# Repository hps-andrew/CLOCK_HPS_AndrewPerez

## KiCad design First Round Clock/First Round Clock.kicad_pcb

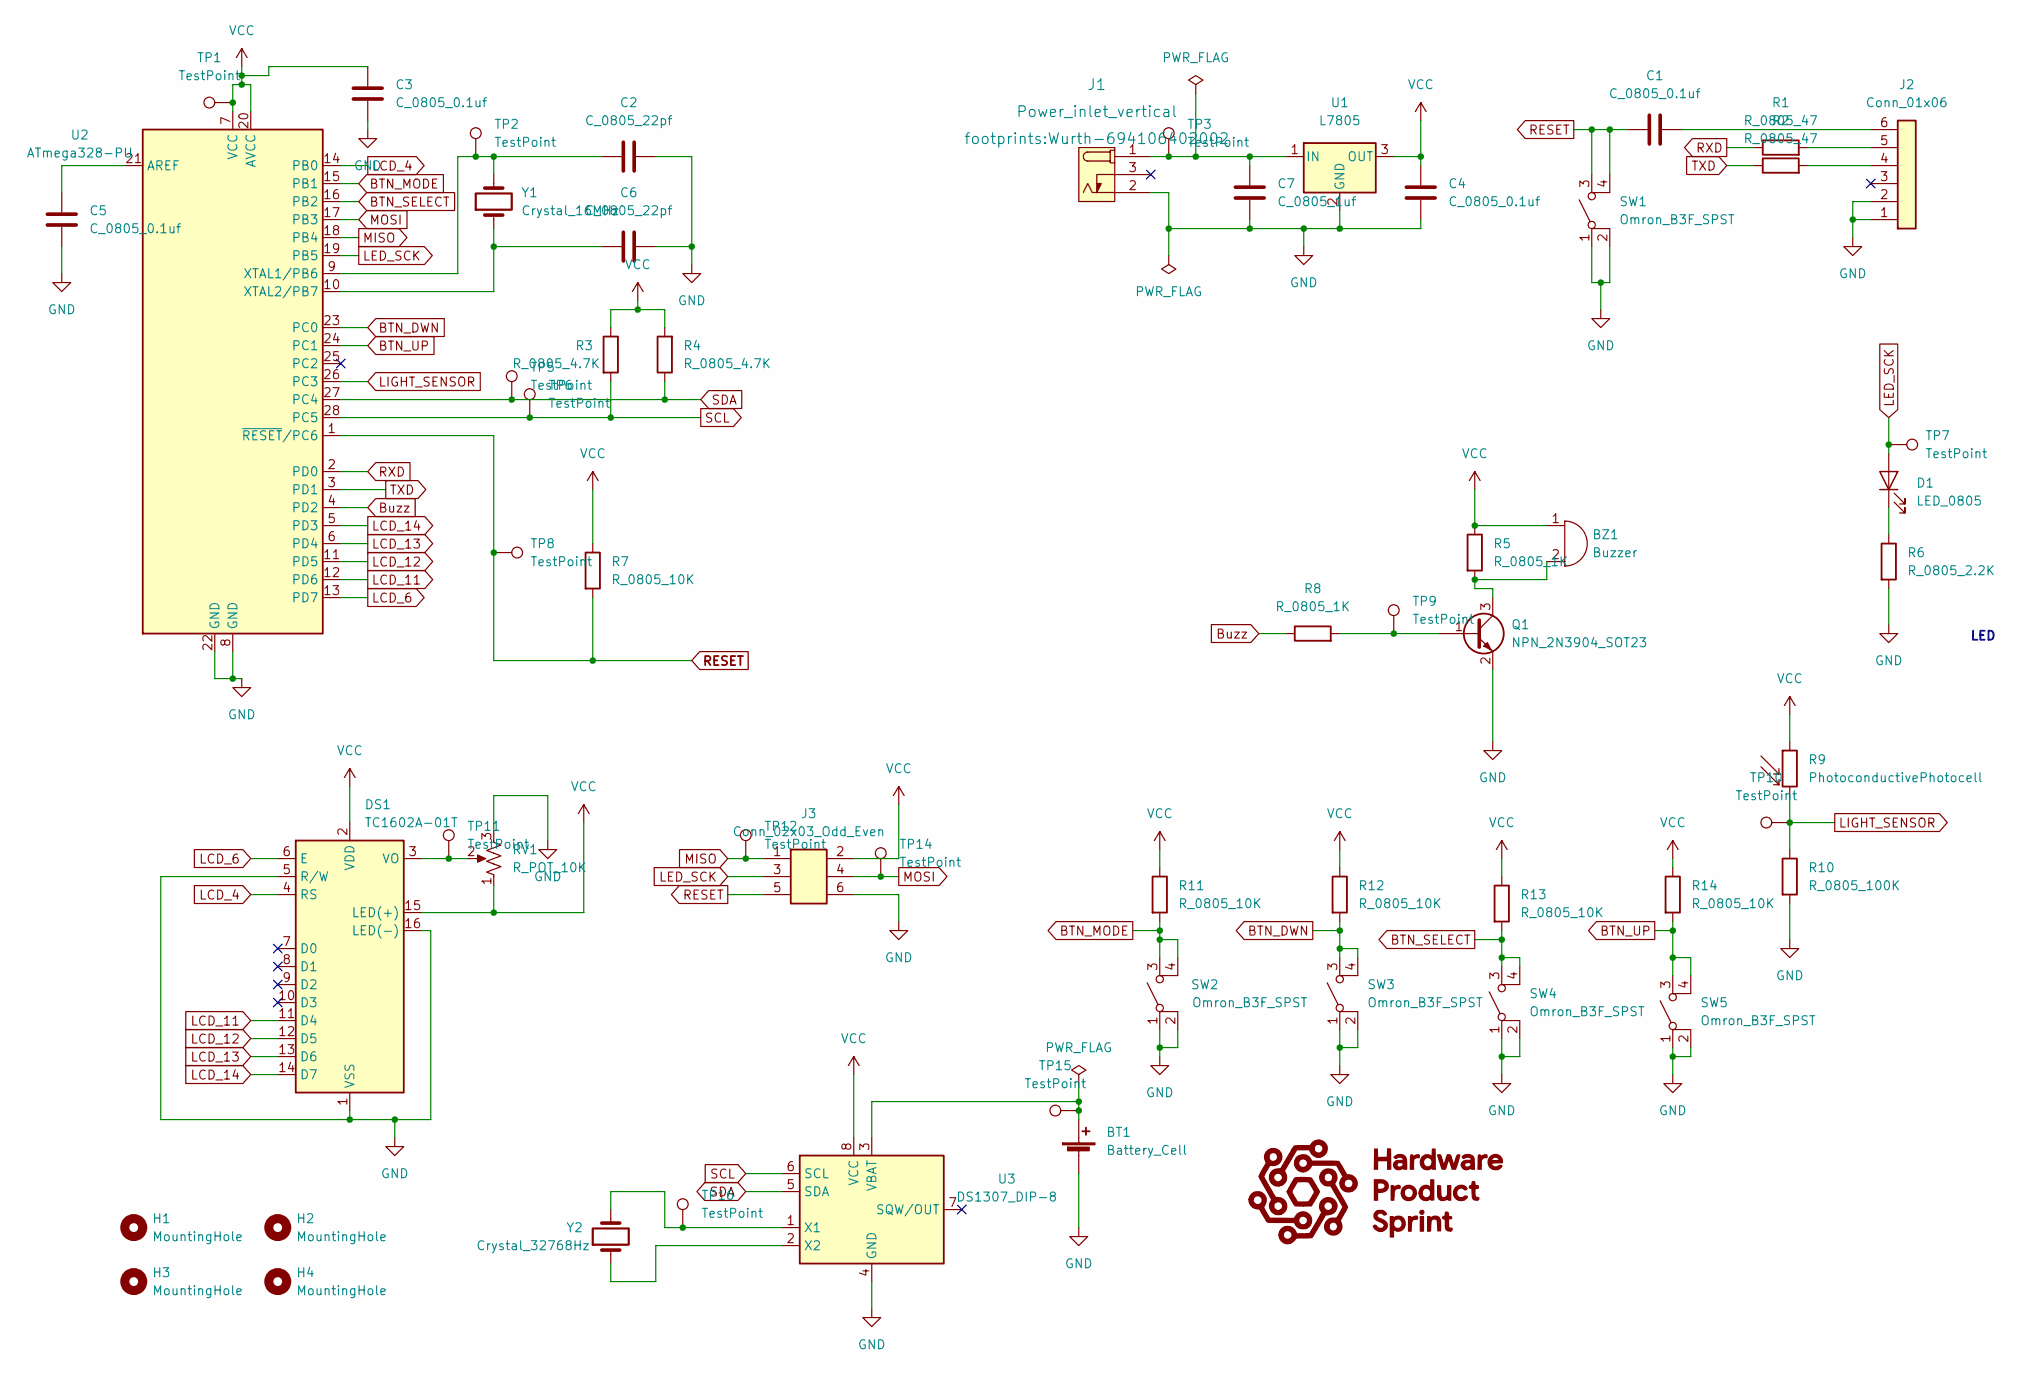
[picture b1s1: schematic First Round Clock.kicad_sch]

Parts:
BT1: Battery_Cell; BatteryHolder_Keystone_106_1x20mm; MPN BS-7; Digikey PN BS-7-ND
BZ1: Buzzer; Buzzer_TDK_PS1240P02BT_D12.2mm_H6.5mm; MPN PS1420P02CT; Digikey PN 445-2526-1-ND
C1, C3, C4, C5: C_0805_0.1uf; C_0805_2012Metric; Voltage N/A; Tolerance N/A; MPN 08055C104KAT2A; Digikey PN 478-1395-1-ND
C2, C6: C_0805_22pf; C_0805_2012Metric; Voltage N/A; Tolerance N/A; MPN CC0805JRNPO9BN220; Digikey PN 311-1103-1-ND
C7: C_0805_1uf; C_0805_2012Metric; Voltage N/A; Tolerance N/A; MPN CC0805KKX7R8BB105; Digikey PN 311-1456-1-ND
D1: LED_0805; LED_0805_2012Metric; MPN 150080RS75000; Digikey PN 732-4984-1-ND
DS1: TC1602A-01T; MPN 1447; Digikey PN 1528-2212-ND
H1, H2, H3, H4: MountingHole; MountingHole_3.2mm_M3
J1: Power_inlet_vertical; Wurth-694106402002; MPN 694106402002; Digikey PN 732-5931-ND
J2: Conn_01x06; PinHeader_1x06_P2.54mm_Vertical; MPN 61300611121; Digikey PN 732-5319-ND
J3: Conn_02x03_Odd_Even; PinHeader_2x03_P2.54mm_Vertical; MPN PRPC003DAAN-RC; Digikey PN S2011EC-03-ND
Q1: NPN_2N3904_SOT23; SOT-23; MPN CMPT3904E TR PBFREE; Digikey PN 1514-CMPT3904ETRPBFREECT-ND
R1, R2: R_0805_47; R_0805_2012Metric; Tolerance N/A; Mouser PN N/A; Digikey PN RC0805FR-0747RL
R3, R4: R_0805_4.7K; R_0805_2012Metric; Tolerance N/A; MPN RC0805FR-074K7L; Digikey PN 311-4.70KCRCT-ND
R5, R8: R_0805_1K; R_0805_2012Metric; Tolerance N/A; Mouser PN N/A; Digikey PN RC0805FR-0710KL
R6: R_0805_2.2K; R_0805_2012Metric; Tolerance N/A; MPN N/A; Digikey PN 311-2.20KCRCT-ND
R7, R11, R12, R13, R14: R_0805_10K; R_0805_2012Metric; Tolerance N/A; MPN RC0805FR-0710KL; Digikey PN 311-10.0KCRCT-ND
R9: PhotoconductivePhotocell; R_LDR_4.9x4.2mm_P2.54mm_Vertical; Voltage N/A; Tolerance N/A; MPN PDV-P8103; Digikey PN PDV-P8103-ND
R10: R_0805_100K; R_0805_2012Metric; Tolerance N/A; MPN RC0805FR-07100KL; Digikey PN 311-100KCRCT-ND
RV1: R_POT_10K; Potentiometer_Bourns_3386P_Vertical; MPN 3386P-1-103TLF; Digikey PN 3386P-103TLF-ND
SW1, SW2, SW3, SW4, SW5: Omron_B3F_SPST; SW_SPST_Omron_B3FS-100xP; MPN B3FS-1000P; Digikey PN SW423CT-ND
TP1, TP2, TP3, TP5, TP6, TP7, TP8, TP9, TP10, TP11, TP12, TP14, TP15, TP16: TestPoint; TestPoint_THTPad_D2.0mm_Drill1.0mm
U1: L7805; TO-252-2; MPN L7805CDT-TR; Digikey PN 497-7255-1-ND
U2: ATmega328-PU; DIP-28_W7.62mm; MPN ED281DT; Digikey PN ED3050-5-ND
U3: DS1307_DIP-8; DIP-8_W7.62mm; MPN A 08-LC-TT; Digikey PN AE9986-ND
Y1: Crystal_16MHz; Crystal_SMD_HC49-SD; MPN ECS-160-20-5PXDN-TR; Digikey PN XC1299CT-ND
Y2: Crystal_32768Hz; Crystal_SMD_2Pin_3.2x1.5mm; MPN Q 0,032768-JTX310-12,5-20-T1-HMR-50K-LF; Digikey PN 1908-1314-1-ND

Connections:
BTN_DWN: R12.2, SW3.3 (B), SW3.4 (B), U2.23 (PC0)
BTN_MODE: R11.2, SW2.3 (B), SW2.4 (B), U2.15 (PB1)
BTN_SELECT: R13.2, SW4.3 (B), SW4.4 (B), U2.16 (PB2)
BTN_UP: R14.2, SW5.3 (B), SW5.4 (B), U2.24 (PC1)
Buzz: R8.1, U2.4 (PD2)
GND: BT1.2 (-), C2.1, C3.2, C4.2, C5.2, C6.2, C7.2, DS1.1 (VSS), DS1.5 (R/W), DS1.16 (LED(-)), J1.2 (OUT), J2.1, J2.2, J3.6, Q1.2 (E), R6.2, R10.2, RV1.3, SW1.1 (A), SW1.2 (A), SW2.1 (A), SW2.2 (A), SW3.1 (A), SW3.2 (A), SW4.1 (A), SW4.2 (A), SW5.1 (A), SW5.2 (A), U1.2 (GND), U2.8 (GND), U2.22 (GND), U3.4 (GND)
LCD_4: DS1.4 (RS), U2.14 (PB0)
LCD_6: DS1.6 (E), U2.13 (PD7)
LCD_11: DS1.11 (D4), U2.12 (PD6)
LCD_12: DS1.12 (D5), U2.11 (PD5)
LCD_13: DS1.13 (D6), U2.6 (PD4)
LCD_14: DS1.14 (D7), U2.5 (PD3)
LED_SCK: D1.2 (A), J3.3, TP7.1, U2.19 (PB5)
LIGHT_SENSOR: R9.2, R10.1, TP10.1, U2.26 (PC3)
MISO: J3.1, TP12.1, U2.18 (PB4)
MOSI: J3.4, TP14.1, U2.17 (PB3)
unnamed: BT1.1 (+), TP15.1, U3.3 (VBAT)
unnamed: BZ1.2 (+), Q1.3 (C), R5.2
unnamed: C1.2, J2.6
unnamed: C2.2, TP2.1, U2.9 (XTAL1/PB6), Y1.2
unnamed: C5.1, U2.21 (AREF)
unnamed: C6.1, U2.10 (XTAL2/PB7), Y1.1
unnamed: D1.1 (K), R6.1
unnamed: DS1.3 (VO), RV1.2, TP11.1
unnamed: C7.1, J1.1 (POLE), TP3.1, U1.1 (IN)
unnamed: J2.4, R2.2
unnamed: J2.5, R1.2
unnamed: Q1.1 (B), R8.2, TP9.1
unnamed: TP16.1, U3.1 (X1), Y2.2
unnamed: U3.2 (X2), Y2.1
RESET: C1.1, J3.5, R7.2, SW1.3 (B), SW1.4 (B), TP8.1, U2.1 (~RESET/PC6)
RXD: R1.1, U2.2 (PD0)
SCL: R3.2, TP6.1, U2.28 (PC5), U3.6 (SCL)
SDA: R4.1, TP5.1, U2.27 (PC4), U3.5 (SDA)
TXD: R2.1, U2.3 (PD1)
VCC: BZ1.1 (-), C3.1, C4.1, DS1.2 (VDD), DS1.15 (LED(+)), J3.2, R3.1, R4.2, R5.1, R7.1, R9.1, R11.1, R12.1, R13.1, R14.1, RV1.1, TP1.1, U1.3 (OUT), U2.7 (VCC), U2.20 (AVCC), U3.8 (VCC)

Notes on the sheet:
LED

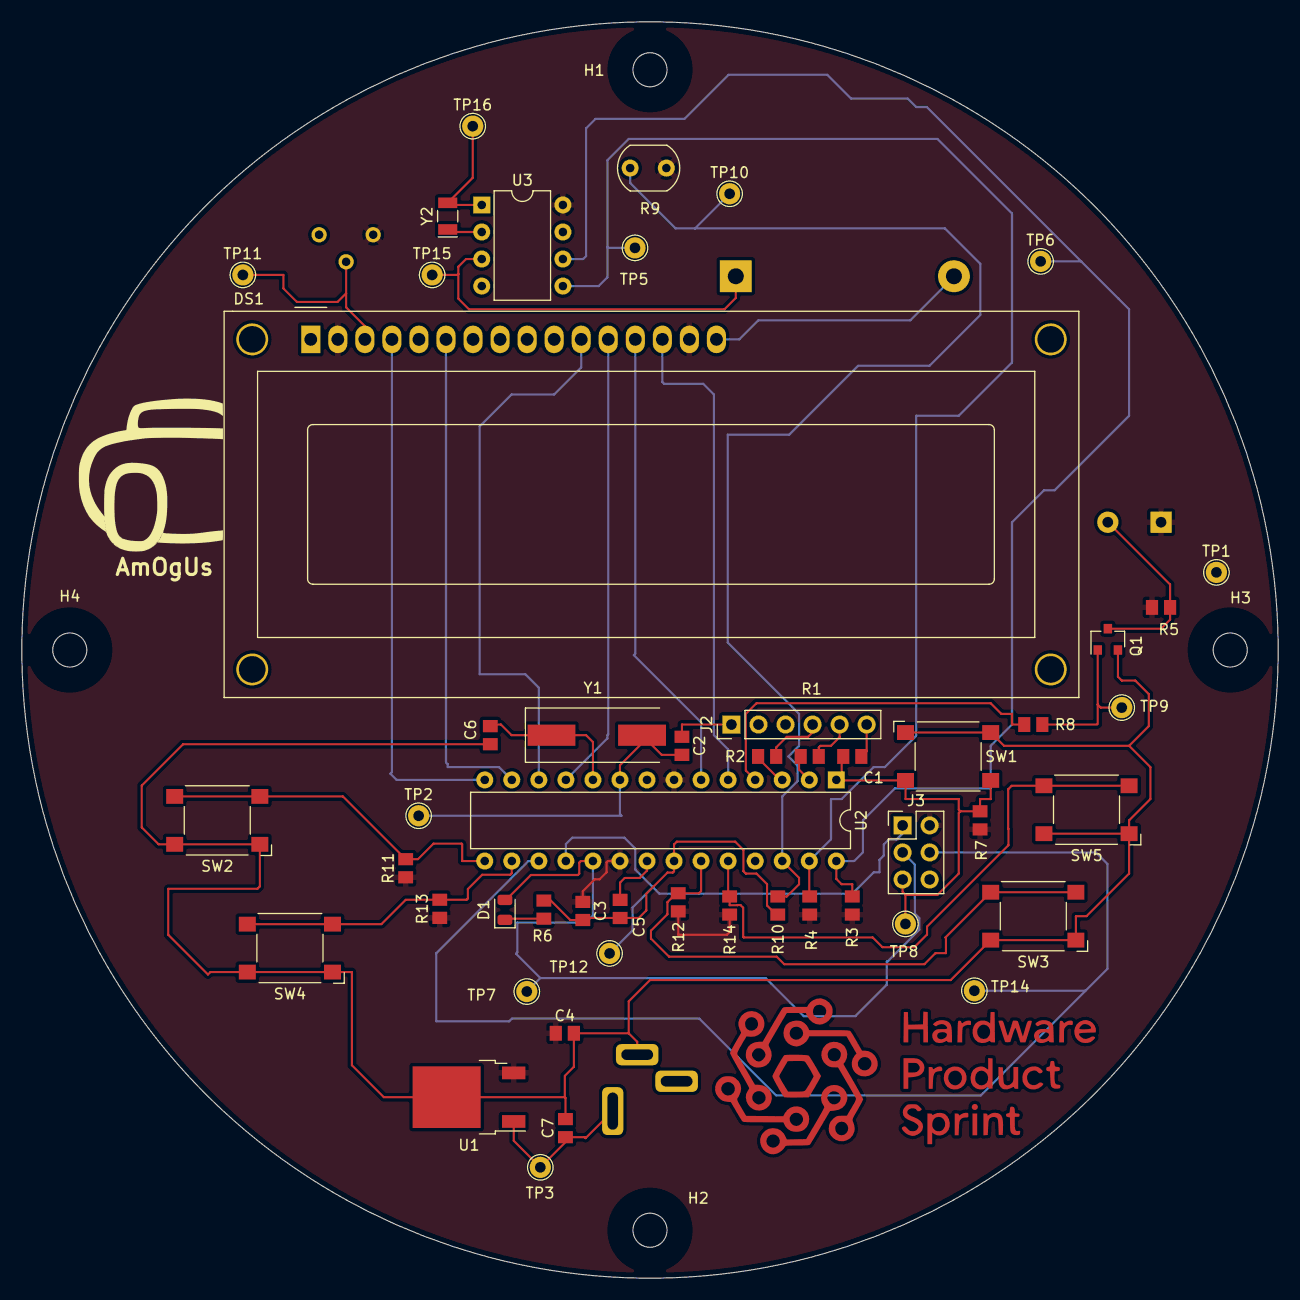
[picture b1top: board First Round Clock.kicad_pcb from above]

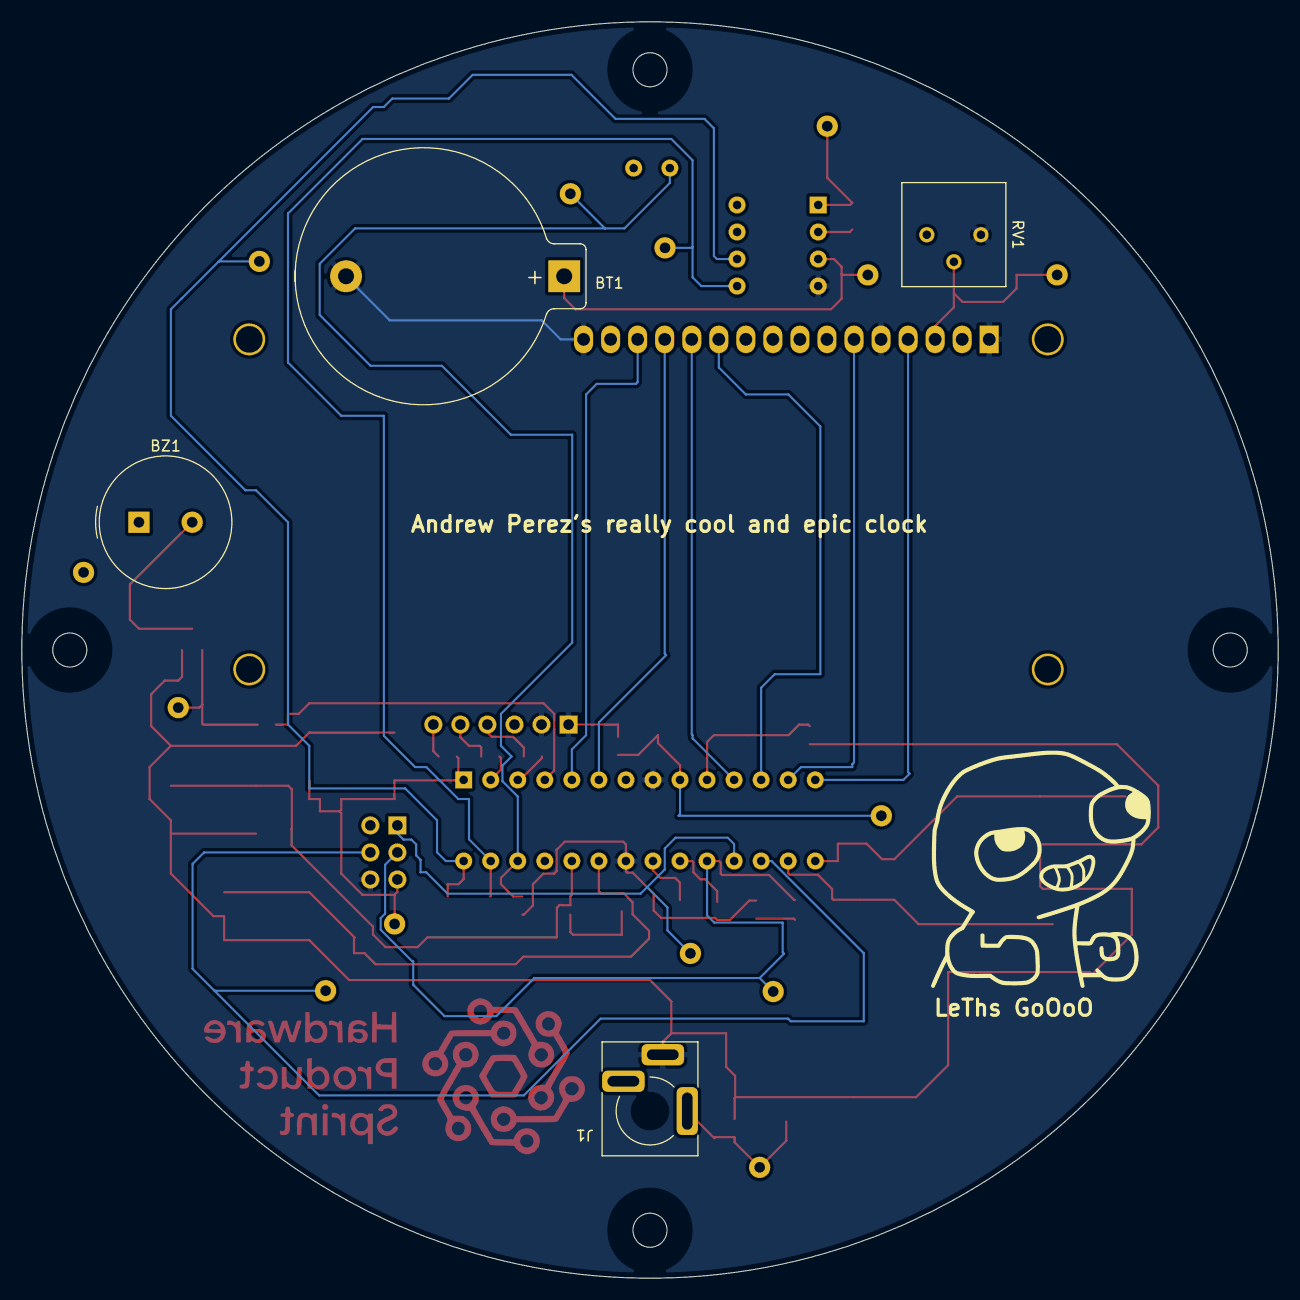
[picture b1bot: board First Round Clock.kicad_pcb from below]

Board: 2 copper layers, 118.0 x 118.0 mm, 60 parts (5 on the bottom side), 36 nets.

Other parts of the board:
AmOgUs: LOGO
LeThs GoOoO: LOGO

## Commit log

2022-06-06 clock
    clock
2022-06-13 NEW_CODE_AND_SCHEMATIC
    Light code and first schematic
2022-06-20 Week2
    Blinking light with button and updated schematic
2022-06-27 Week 3 deliverables
    updated schematic and clock code
2022-07-09 Week 4
    Final schematic update hopefully
2022-07-10 Create _autosave-First Round Clock.kicad_sch
    new
2022-07-14 Updated BOM and schematic
    New and final BOM
2022-07-18 Week6
    All deliverables for week 6
2022-07-18 zip
    zip files with the gbr and drl
2022-07-22 Final clock
    Final gerber out for clock
2022-07-22 final fix for clock
    Final clock used and fixed
2022-08-26 LastCommittoMain
    All code used throughout the program
